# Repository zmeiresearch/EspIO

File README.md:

# EspIO

This is a simple carrier board for ESP32-DevKitC (30-pin version) that implements a number of I/O channels:
- 8 Digital Inputs with protection and solder-time input range selection. Default values in schematic are for 12V input
  but this can easily be extended up to ~200V by proper resistor selection.
- 8 Digital Outputs, either buffered push-pull or Open Collector with on-board pull-ups.
- RS-485 serial interface

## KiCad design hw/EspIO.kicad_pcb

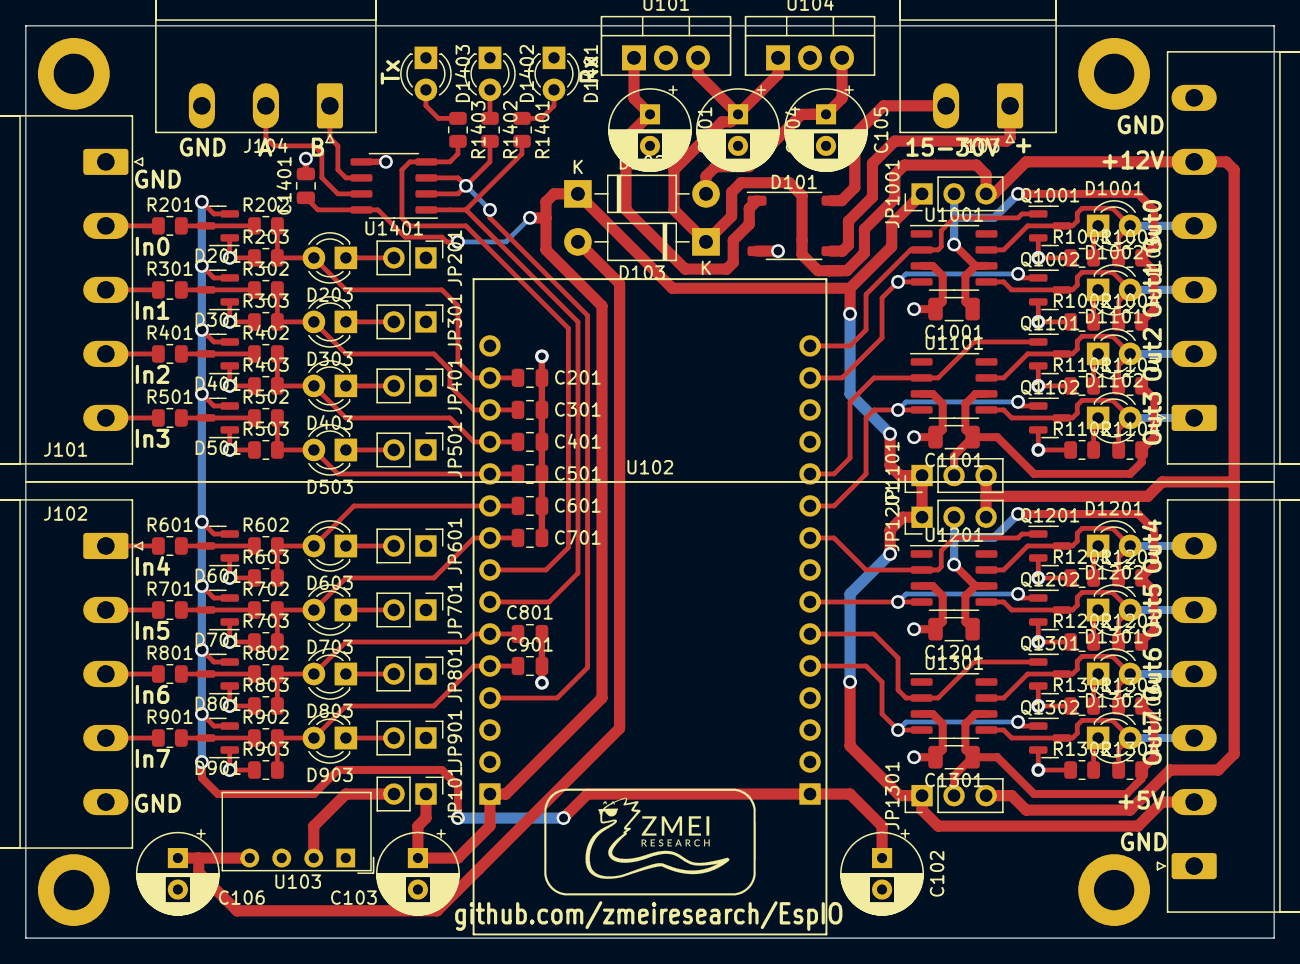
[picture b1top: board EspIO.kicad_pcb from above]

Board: 2 copper layers, 99.1 x 72.4 mm, 132 parts (0 on the bottom side), 78 nets.

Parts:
C101, C102, C103, C104, C105: 100uF/16V; CP_Radial_D6.3mm_P2.50mm
C106: 22uF/25V; CP_Radial_D6.3mm_P2.50mm
C201, C301, C401, C501, C601, C701, C801, C901: 10nF; C_0805_2012Metric
C1001, C1101, C1201, C1301: 10nF; C_1206_3216Metric
C1401: 100nF; C_0805_2012Metric
D101: MDB10S; TSSOP-4_4.4x5mm_P4mm
D102, D103: 1N5818; D_DO-41_SOD81_P10.16mm_Horizontal
D201, D301, D401, D501, D601, D701, D801, D901: BAT54S; SOT-23
D203, D303, D403, D503, D603, D703, D803, D903, D1001, D1002, D1101, D1102, D1201, D1202, D1301, D1302: LED; LED_D3.0mm
D1401: Rx; LED_D3.0mm
D1402: TE; LED_D3.0mm
D1403: Tx; LED_D3.0mm
H101, H102, H103, H104: MountingHole; MountingHole_3.2mm_M3_ISO7380_Pad
J101, J102: 2EDGR-5.08-05P-14-00AH; PhoenixContact_MSTBA_2,5_5-G-5,08_1x05_P5.08mm_Horizontal
J103: Screw_Terminal_01x02; PhoenixContact_MSTBA_2,5_2-G-5,08_1x02_P5.08mm_Horizontal
J104: Screw_Terminal_01x03; PhoenixContact_MSTBA_2,5_3-G-5,08_1x03_P5.08mm_Horizontal
J105, J106: Screw_Terminal_01x06; PhoenixContact_MSTBA_2,5_6-G-5,08_1x06_P5.08mm_Horizontal
JP101, JP201, JP301, JP401, JP501, JP601, JP701, JP801, JP901: Jumper_2_Open; PinHeader_1x02_P2.54mm_Vertical
JP1001, JP1101, JP1201, JP1301: Jumper_3_Open; PinHeader_1x03_P2.54mm_Vertical
Q1001, Q1002, Q1101, Q1102, Q1201, Q1202, Q1301, Q1302: BCR141; SOT-23
R201, R301, R401, R501, R601, R701, R801, R901: 2.2k; R_0805_2012Metric
R202, R302, R402, R502, R602, R702, R802, R902, R1001, R1002, R1003, R1004, R1101, R1102, R1103, R1104, R1201, R1202, R1203, R1204, R1301, R1302, R1303, R1304, R1401, R1402, R1403: 1k; R_0805_2012Metric
R203, R303, R403, R503, R603, R703, R803, R903: 22k; R_0805_2012Metric
U101: LM7812_TO220; TO-220-3_Vertical
U102: ESP32DevKit_30pin
U103: AM1SS-0512SJZ; Converter_DCDC_AM1SS
U104: LM7805_TO220; TO-220-3_Vertical
U1001, U1101, U1201, U1301: TC4427; SO-8_3.9x4.9mm_P1.27mm
U1401: SN75176AP; SO-8_3.9x4.9mm_P1.27mm

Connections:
+3.3V: C102.1, D201.2 (K), D301.2 (K), D401.2 (K), D501.2 (K), D601.2 (K), D701.2 (K), D801.2 (K), D901.2 (K), U102.1 (3V3)
+5V: C103.1, C1401.1, D102.1 (K), J106.2, JP101.1 (A), JP1001.1 (A), JP1101.1 (A), JP1201.1 (A), JP1301.1 (A), U102.30 (Vin), U1401.8 (VCC)
+12V: C104.1, D103.1 (K), J105.5, JP1001.3 (B), JP1101.3 (B), JP1201.3 (B), JP1301.3 (B), U101.3 (VO), U104.1 (VI)
/DI0: J101.2, R201.1
/DI0_: C201.1, D203.2 (A), R202.2, R203.2, U102.17 (SP/G36/ADC0)
/DI1: J101.3, R301.1
/DI1_: C301.1, D303.2 (A), R302.2, R303.2, U102.18 (SN/G39/ADC3)
/DI2: J101.4, R401.1
/DI2_: C401.1, D403.2 (A), R402.2, R403.2, U102.19 (G34/ADC6)
/DI3: J101.5, R501.1
/DI3_: C501.1, D503.2 (A), R502.2, R503.2, U102.20 (G35/ADC7)
/DI4: J102.1, R601.1
/DI4_: C601.1, D603.2 (A), R602.2, R603.2, U102.21 (G32/ADC4/T9)
/DI5: J102.2, R701.1
/DI5_: C701.1, D703.2 (A), R702.2, R703.2, U102.22 (G33/ADC5/T8)
/DI6: J102.3, R801.1
/DI6_: C801.1, D803.2 (A), R802.2, R803.2, U102.25 (G27/ADC17/T7)
/DI7: J102.4, R901.1
/DI7_: C901.1, D903.2 (A), R902.2, R903.2, U102.26 (G14/ADC16/T6/SPI_CLK)
/DO0: D1001.2 (A), J105.4, Q1001.3 (C), R1003.1, U1001.7 (OutA)
/DO0_: Q1001.1 (B), U102.15 (G23/VSPI_MOSI), U1001.2 (InA)
/DO1: D1002.2 (A), J105.3, Q1002.3 (C), R1004.1, U1001.5 (OutB)
/DO1_: Q1002.1 (B), U102.14 (G22/I2C_SCL), U1001.4 (InB)
/DO2: D1101.2 (A), J105.2, Q1101.3 (C), R1103.1, U1101.7 (OutA)
/DO2_: Q1101.1 (B), U102.11 (G21/I2C_SDA), U1101.2 (InA)
/DO3: D1102.2 (A), J105.1, Q1102.3 (C), R1104.1, U1101.5 (OutB)
/DO3_: Q1102.1 (B), U102.10 (G19/VSPI_MISO), U1101.4 (InB)
/DO4: D1201.2 (A), J106.6, Q1201.3 (C), R1203.1, U1201.7 (OutA)
/DO4_: Q1201.1 (B), U102.9 (G18/VSPI_SCK), U1201.2 (InA)
/DO5: D1202.2 (A), J106.5, Q1202.3 (C), R1204.1, U1201.5 (OutB)
/DO5_: Q1202.1 (B), U102.7 (G17/TX2), U1201.4 (InB)
/DO6: D1301.2 (A), J106.4, Q1301.3 (C), R1303.1, U1301.7 (OutA)
/DO6_: Q1301.1 (B), U102.6 (G16/RX2), U1301.2 (InA)
/DO7: D1302.2 (A), J106.3, Q1302.3 (C), R1304.1, U1301.5 (OutB)
/DO7_: Q1302.1 (B), U102.5 (G4/ADC010/T0), U1301.4 (InB)
/RS485/A: J104.2, U1401.7 (B)
/RS485/B: J104.1, U1401.6 (A)
/Rx: R1401.2, U102.24 (G26/ADC19/DAC2), U1401.1 (R)
/Tx: R1403.2, U102.23 (G25/ADC18/DAC1), U1401.4 (D)
/Tx/~Rx: R1402.2, U102.27 (G12/ADC15/T5/SPI_MISO), U1401.2 (~RE), U1401.3 (DE)
GND: C101.2, C102.2, C103.2, C104.2, C105.2, C106.2, C201.2, C301.2, C401.2, C501.2, C601.2, C701.2, C801.2, C901.2, C1001.2, C1101.2, C1201.2, C1301.2, C1401.2, D101.2 (-), D201.1 (A), D301.1 (A), D401.1 (A), D501.1 (A), D601.1 (A), D701.1 (A), D801.1 (A), D901.1 (A), D1401.1 (K), D1402.1 (K), D1403.1 (K), J101.1, J102.5, J104.3, J105.6, J106.1, JP201.1 (A), JP301.1 (A), JP401.1 (A), JP501.1 (A), JP601.1 (A), JP701.1 (A), JP801.1 (A), JP901.1 (A), Q1001.2 (E), Q1002.2 (E), Q1101.2 (E), Q1102.2 (E), Q1201.2 (E), Q1202.2 (E), Q1301.2 (E), Q1302.2 (E), R203.1, R303.1, R403.1, R503.1, R603.1, R703.1, R803.1, R903.1, R1001.1, R1002.1, R1101.1, R1102.1, R1201.1, R1202.1, R1301.1, R1302.1, U101.2 (GND), U102.2 (GND), U102.29 (GND), U103.1 (-Vin), U103.3 (-Vout), U104.2 (GND), U1001.3 (GND), U1101.3 (GND), U1201.3 (GND), U1301.3 (GND), U1401.5 (GND)
unnamed: C101.1, D101.1 (+), U101.1 (VI)
unnamed: C105.1, D102.2 (A), U104.3 (VO)
unnamed: C106.1, D103.2 (A), U103.4 (+Vout)
unnamed: D201.3 (COM), R201.2, R202.1
unnamed: D203.1 (K), JP201.2 (B)
unnamed: D301.3 (COM), R301.2, R302.1
unnamed: D303.1 (K), JP301.2 (B)
unnamed: D401.3 (COM), R401.2, R402.1
unnamed: D403.1 (K), JP401.2 (B)
unnamed: D501.3 (COM), R501.2, R502.1
unnamed: D503.1 (K), JP501.2 (B)
unnamed: D601.3 (COM), R601.2, R602.1
unnamed: D603.1 (K), JP601.2 (B)
unnamed: D701.3 (COM), R701.2, R702.1
unnamed: D703.1 (K), JP701.2 (B)
unnamed: D801.3 (COM), R801.2, R802.1
unnamed: D803.1 (K), JP801.2 (B)
unnamed: D901.3 (COM), R901.2, R902.1
unnamed: D903.1 (K), JP901.2 (B)
unnamed: D1001.1 (K), R1001.2
unnamed: D1002.1 (K), R1002.2
unnamed: D1101.1 (K), R1101.2
unnamed: D1102.1 (K), R1102.2
unnamed: D1201.1 (K), R1201.2
unnamed: D1202.1 (K), R1202.2
unnamed: D1301.1 (K), R1301.2
unnamed: D1302.1 (K), R1302.2
unnamed: D1401.2 (A), R1401.1
unnamed: D1402.2 (A), R1402.1
unnamed: D1403.2 (A), R1403.1
unnamed: D101.3, J103.1
unnamed: D101.4, J103.2
unnamed: JP101.2 (B), U103.2 (+Vin)
unnamed: C1001.1, JP1001.2 (C), R1003.2, R1004.2, U1001.6 (Vdd)
unnamed: C1101.1, JP1101.2 (C), R1103.2, R1104.2, U1101.6 (Vdd)
unnamed: C1201.1, JP1201.2 (C), R1203.2, R1204.2, U1201.6 (Vdd)
unnamed: C1301.1, JP1301.2 (C), R1303.2, R1304.2, U1301.6 (Vdd)
